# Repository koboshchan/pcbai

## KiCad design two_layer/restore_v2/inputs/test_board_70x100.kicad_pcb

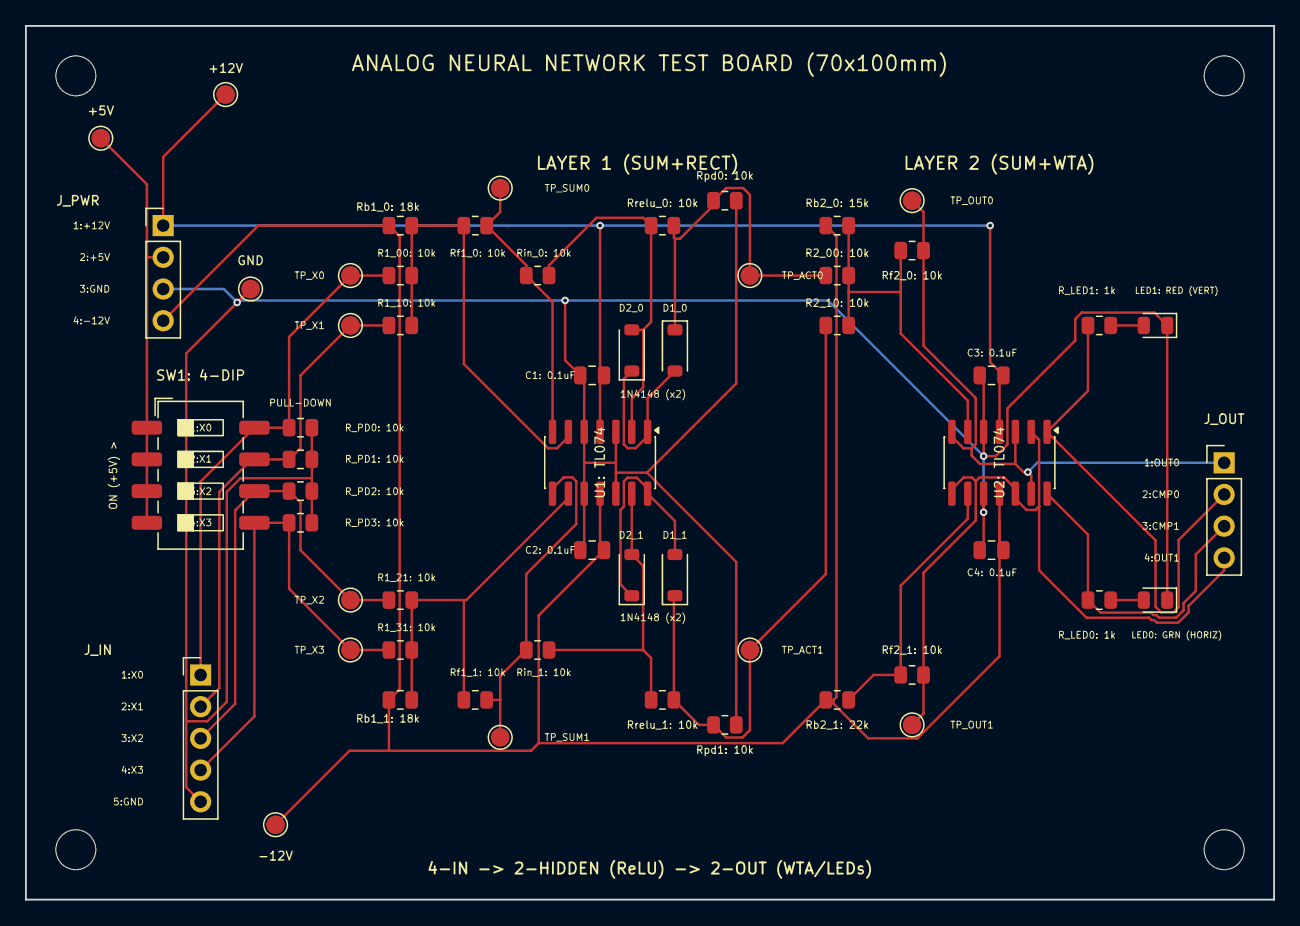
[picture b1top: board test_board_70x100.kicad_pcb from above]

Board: 2 copper layers, 100.0 x 70.0 mm, 60 parts (0 on the bottom side), 26 nets.

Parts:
C1, C2, C3, C4: 0.1uF; C_0805_2012Metric
D1_0, D1_1, D2_0, D2_1: 1N4148; D_SOD-123
H1, H2, H3, H4: M3; MountingHole_3.2mm_M3
J_IN: X0..X3/GND; PinHeader_1x05_P2.54mm_Vertical
J_OUT: OUT; PinHeader_1x04_P2.54mm_Vertical
J_PWR: PWR; PinHeader_1x04_P2.54mm_Vertical
LED0: Green_Horiz; LED_0805_2012Metric
LED1: Red_Vert; LED_0805_2012Metric
R1_00, R1_10, R1_21, R1_31, R2_00, R2_10: 10k; R_0805_2012Metric
R_LED0, R_LED1: 1k; R_0805_2012Metric
R_PD0, R_PD1, R_PD2, R_PD3: 10k; R_0805_2012Metric
Rb1_0, Rb1_1: 18k; R_0805_2012Metric
Rb2_0: 15k; R_0805_2012Metric
Rb2_1: 22k; R_0805_2012Metric
Rf1_0, Rf1_1, Rf2_0, Rf2_1: 10k; R_0805_2012Metric
Rin_0, Rin_1: 10k; R_0805_2012Metric
Rpd_act0, Rpd_act1: 10k; R_0805_2012Metric
Rrelu_0, Rrelu_1: 10k; R_0805_2012Metric
SW1: 4-DIP; SW_DIP_SPSTx04_Slide_6.7x11.72mm_W8.61mm_P2.54mm_LowProfile
TP_+5V: +5V; TestPoint_Pad_D1.5mm
TP_+12V: +12V; TestPoint_Pad_D1.5mm
TP_-12V: -12V; TestPoint_Pad_D1.5mm
TP_ACT0: V_ACT0; TestPoint_Pad_D1.5mm
TP_ACT1: V_ACT1; TestPoint_Pad_D1.5mm
TP_GND: GND; TestPoint_Pad_D1.5mm
TP_OUT0: V_OUT0; TestPoint_Pad_D1.5mm
TP_OUT1: V_OUT1; TestPoint_Pad_D1.5mm
TP_SUM0: V_SUM0; TestPoint_Pad_D1.5mm
TP_SUM1: V_SUM1; TestPoint_Pad_D1.5mm
TP_X0: X0; TestPoint_Pad_D1.5mm
TP_X1: X1; TestPoint_Pad_D1.5mm
TP_X2: X2; TestPoint_Pad_D1.5mm
TP_X3: X3; TestPoint_Pad_D1.5mm
U1, U2: TL074; SOIC-14_3.9x8.7mm_P1.27mm

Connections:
+5V: J_PWR.2, SW1.1, SW1.2, SW1.3, SW1.4, TP_+5V.1
+12V: C1.2, C3.2, J_PWR.1, TP_+12V.1, U1.4, U2.4
-12V: C2.2, C4.2, J_PWR.4, Rb1_0.1, Rb1_1.1, Rb2_0.1, Rb2_1.1, TP_-12V.1, U1.11, U2.11
CMP_OUT0: J_OUT.2, R_LED1.1, U2.1
CMP_OUT1: J_OUT.3, R_LED0.1, U2.14
GND: C1.1, C2.1, C3.1, C4.1, J_IN.5, J_PWR.3, LED0.1, LED1.1, R_PD0.2, R_PD1.2, R_PD2.2, R_PD3.2, Rpd_act0.2, Rpd_act1.2, TP_GND.1, U1.3, U1.5, U1.10, U1.12, U2.5, U2.10
LED0_A: LED0.2, R_LED0.2
LED1_A: LED1.2, R_LED1.2
RECT_NODE_0: D2_0.2, Rin_0.2, Rrelu_0.1, U1.2
RECT_NODE_1: D2_1.2, Rin_1.2, Rrelu_1.1, U1.13
RECT_OUT_0: D1_0.2, D2_0.1, U1.1
RECT_OUT_1: D1_1.2, D2_1.1, U1.14
SUM2_NODE_0: R2_00.2, R2_10.2, Rb2_0.2, Rf2_0.1, U2.6
SUM2_NODE_1: Rb2_1.2, Rf2_1.1, U2.9
SUM_NODE_0: R1_00.2, R1_10.2, Rb1_0.2, Rf1_0.1, U1.6
SUM_NODE_1: R1_21.2, R1_31.2, Rb1_1.2, Rf1_1.1, U1.9
V_ACT0: D1_0.1, R2_00.1, Rpd_act0.1, Rrelu_0.2, TP_ACT0.1
V_ACT1: D1_1.1, R2_10.1, Rpd_act1.1, Rrelu_1.2, TP_ACT1.1
V_OUT0: J_OUT.1, Rf2_0.2, TP_OUT0.1, U2.3, U2.7, U2.13
V_OUT1: J_OUT.4, Rf2_1.2, TP_OUT1.1, U2.2, U2.8, U2.12
V_SUM0: Rf1_0.2, Rin_0.1, TP_SUM0.1, U1.7
V_SUM1: Rf1_1.2, Rin_1.1, TP_SUM1.1, U1.8
X0: J_IN.1, R1_00.1, R_PD0.1, SW1.8, TP_X0.1
X1: J_IN.2, R1_10.1, R_PD1.1, SW1.7, TP_X1.1
X2: J_IN.3, R1_21.1, R_PD2.1, SW1.6, TP_X2.1
X3: J_IN.4, R1_31.1, R_PD3.1, SW1.5, TP_X3.1

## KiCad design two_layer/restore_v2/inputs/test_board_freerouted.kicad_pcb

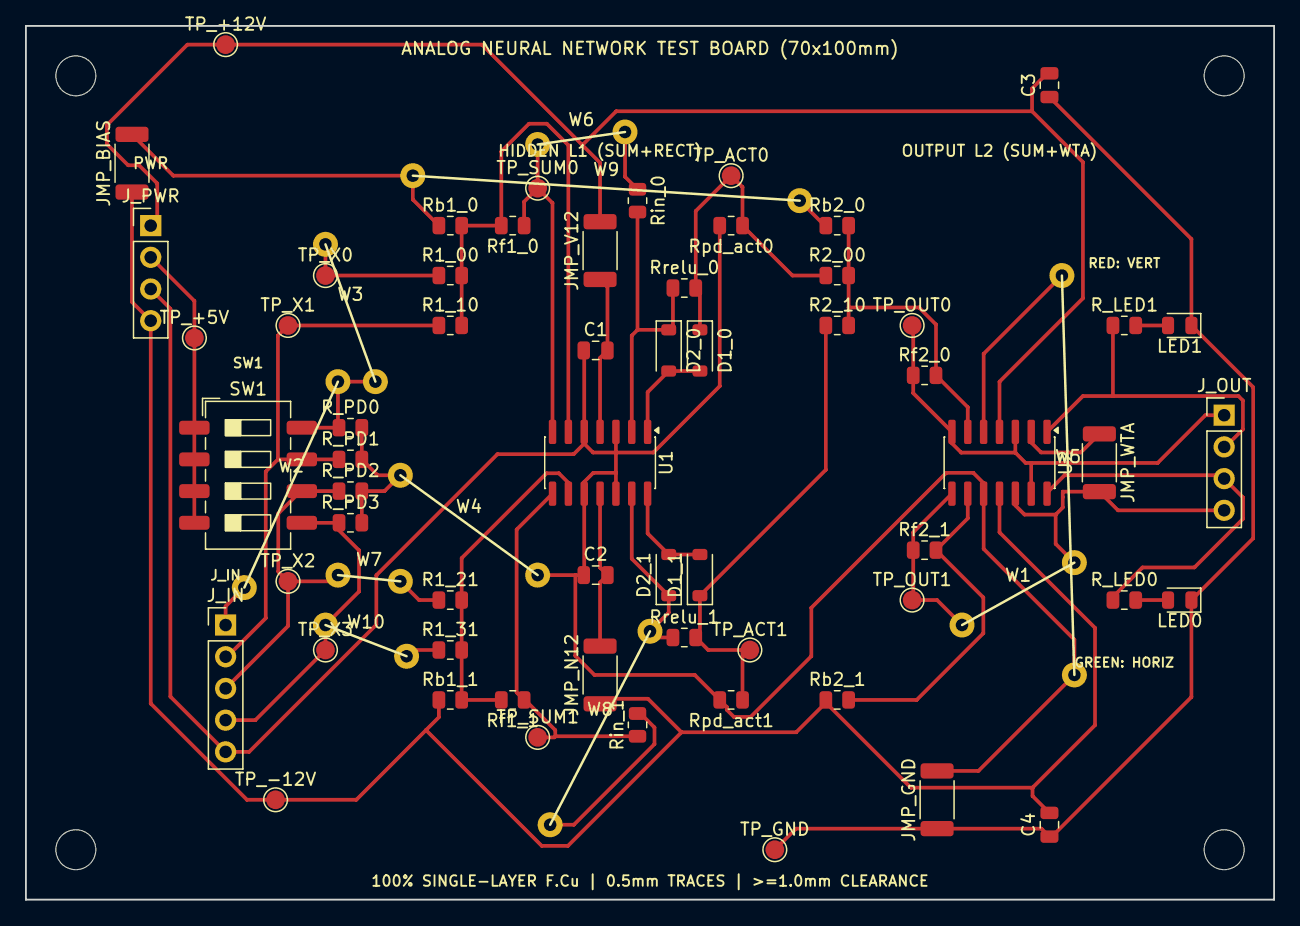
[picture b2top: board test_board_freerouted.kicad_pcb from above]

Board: 2 copper layers, 100.0 x 70.0 mm, 75 parts (0 on the bottom side), 41 nets.

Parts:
C1, C2, C3, C4: 0.1uF; C_0805_2012Metric
D1_0, D1_1, D2_0, D2_1: 1N4148; D_SOD-123
H1, H2, H3, H4: M3; MountingHole_3.2mm_M3
JMP_BIAS: 0R; R_2010_5025Metric
JMP_GND: 0R; R_2010_5025Metric
JMP_N12: 0R; R_2010_5025Metric
JMP_V12: 0R; R_2010_5025Metric
JMP_WTA: 0R; R_2010_5025Metric
J_IN: X0..X3/GND; PinHeader_1x05_P2.54mm_Vertical
J_OUT: OUT; PinHeader_1x04_P2.54mm_Vertical
J_PWR: PWR; PinHeader_1x04_P2.54mm_Vertical
LED0: Green_Horiz; LED_0805_2012Metric
LED1: Red_Vert; LED_0805_2012Metric
R1_00, R1_10, R1_21, R1_31, R2_00, R2_10: 10k; R_0805_2012Metric
R_LED0, R_LED1: 1k; R_0805_2012Metric
R_PD0, R_PD1, R_PD2, R_PD3: 10k; R_0805_2012Metric
Rb1_0, Rb1_1: 18k; R_0805_2012Metric
Rb2_0: 15k; R_0805_2012Metric
Rb2_1: 22k; R_0805_2012Metric
Rf1_0, Rf1_1, Rf2_0, Rf2_1: 10k; R_0805_2012Metric
Rin_0, Rin_1: 10k; R_0805_2012Metric
Rpd_act0, Rpd_act1: 10k; R_0805_2012Metric
Rrelu_0, Rrelu_1: 10k; R_0805_2012Metric
SW1: 4-DIP; SW_DIP_SPSTx04_Slide_6.7x11.72mm_W8.61mm_P2.54mm_LowProfile
TP_+5V: +5V; TestPoint_Pad_D1.5mm
TP_+12V: +12V; TestPoint_Pad_D1.5mm
TP_-12V: -12V; TestPoint_Pad_D1.5mm
TP_ACT0: V_ACT0; TestPoint_Pad_D1.5mm
TP_ACT1: V_ACT1; TestPoint_Pad_D1.5mm
TP_GND: GND_SOUTH; TestPoint_Pad_D1.5mm
TP_OUT0: V_OUT0; TestPoint_Pad_D1.5mm
TP_OUT1: V_OUT1; TestPoint_Pad_D1.5mm
TP_SUM0: V_SUM0; TestPoint_Pad_D1.5mm
TP_SUM1: V_SUM1; TestPoint_Pad_D1.5mm
TP_X0: X0; TestPoint_Pad_D1.5mm
TP_X1: X1; TestPoint_Pad_D1.5mm
TP_X2: X2; TestPoint_Pad_D1.5mm
TP_X3: X3; TestPoint_Pad_D1.5mm
U1, U2: TL074; SOIC-14_3.9x8.7mm_P1.27mm
W1, W2, W3, W4, W5, W6, W7, W8, W9, W10: Jumper_Wire

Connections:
+5V: J_PWR.2, SW1.1, SW1.2, SW1.3, SW1.4, TP_+5V.1
+12V: C3.2, JMP_V12.2, J_PWR.1, TP_+12V.1, U2.4
+12V_U1: C1.2, JMP_V12.1, U1.4
-12V: C4.2, JMP_BIAS.1, JMP_N12.1, J_PWR.4, Rb1_1.1, Rb2_1.1, TP_-12V.1, U2.11
-12V_NORTH: JMP_BIAS.2, Rb1_0.1, W9.2
-12V_NORTH_B: Rb2_0.1, W9.1
-12V_U1: C2.2, JMP_N12.2, U1.11
CMP_OUT0: J_OUT.2, R_LED1.1, U2.1
CMP_OUT1: J_OUT.3, R_LED0.1, U2.14
GND: C1.1, C2.1, JMP_GND.2, J_IN.5, J_PWR.3, Rpd_act0.2, Rpd_act1.2, U1.3, U1.5, U1.10, U1.12, U2.10, W4.2, W5.2
GND_SOUTH: C3.1, C4.1, JMP_GND.1, LED0.1, LED1.1, TP_GND.1
GND_U2_5: U2.5, W5.1
GND_WEST: R_PD0.2, R_PD1.2, R_PD2.2, R_PD3.2, W4.1
LED0_A: LED0.2, R_LED0.2
LED1_A: LED1.2, R_LED1.2
RECT_NODE_0: D2_0.1, Rin_0.2, Rrelu_0.1, U1.2
RECT_NODE_1: D2_1.1, Rrelu_1.1, U1.13, W8.2
RECT_NODE_1_IN: Rin_1.2, W8.1
RECT_OUT_0: D1_0.2, D2_0.2, U1.1
RECT_OUT_1: D1_1.2, D2_1.2, U1.14
SUM2_NODE_0: R2_00.2, R2_10.2, Rb2_0.2, Rf2_0.2, U2.6
SUM2_NODE_1: Rb2_1.2, Rf2_1.2, U2.9
SUM_NODE_0: R1_00.2, R1_10.2, Rb1_0.2, Rf1_0.2, U1.6
SUM_NODE_1: R1_21.2, R1_31.2, Rb1_1.2, Rf1_1.2, U1.9
V_ACT0: D1_0.1, R2_00.1, Rpd_act0.1, Rrelu_0.2, TP_ACT0.1
V_ACT1: D1_1.1, R2_10.1, Rpd_act1.1, Rrelu_1.2, TP_ACT1.1
V_OUT0: J_OUT.1, Rf2_0.1, TP_OUT0.1, U2.3, U2.7, U2.13
V_OUT1: JMP_WTA.2, J_OUT.4, U2.12, W1.2
V_OUT1_A: Rf2_1.1, TP_OUT1.1, U2.8, W1.1
V_OUT1_JMP: JMP_WTA.1, U2.2
V_SUM0: Rf1_0.1, TP_SUM0.1, U1.7, W6.2
V_SUM0_IN: Rin_0.1, W6.1
V_SUM1: Rf1_1.1, Rin_1.1, TP_SUM1.1, U1.8
X0: R_PD0.1, SW1.8, W2.2, W3.1
X0_IN: J_IN.1, W2.1
X0_NORTH: R1_00.1, TP_X0.1, W3.2
X1: J_IN.2, R1_10.1, R_PD1.1, SW1.7, TP_X1.1
X2: J_IN.3, R_PD2.1, SW1.6, TP_X2.1, W7.2
X2_R1: R1_21.1, W7.1
X3: J_IN.4, R_PD3.1, SW1.5, TP_X3.1, W10.1
X3_R1: R1_31.1, W10.2

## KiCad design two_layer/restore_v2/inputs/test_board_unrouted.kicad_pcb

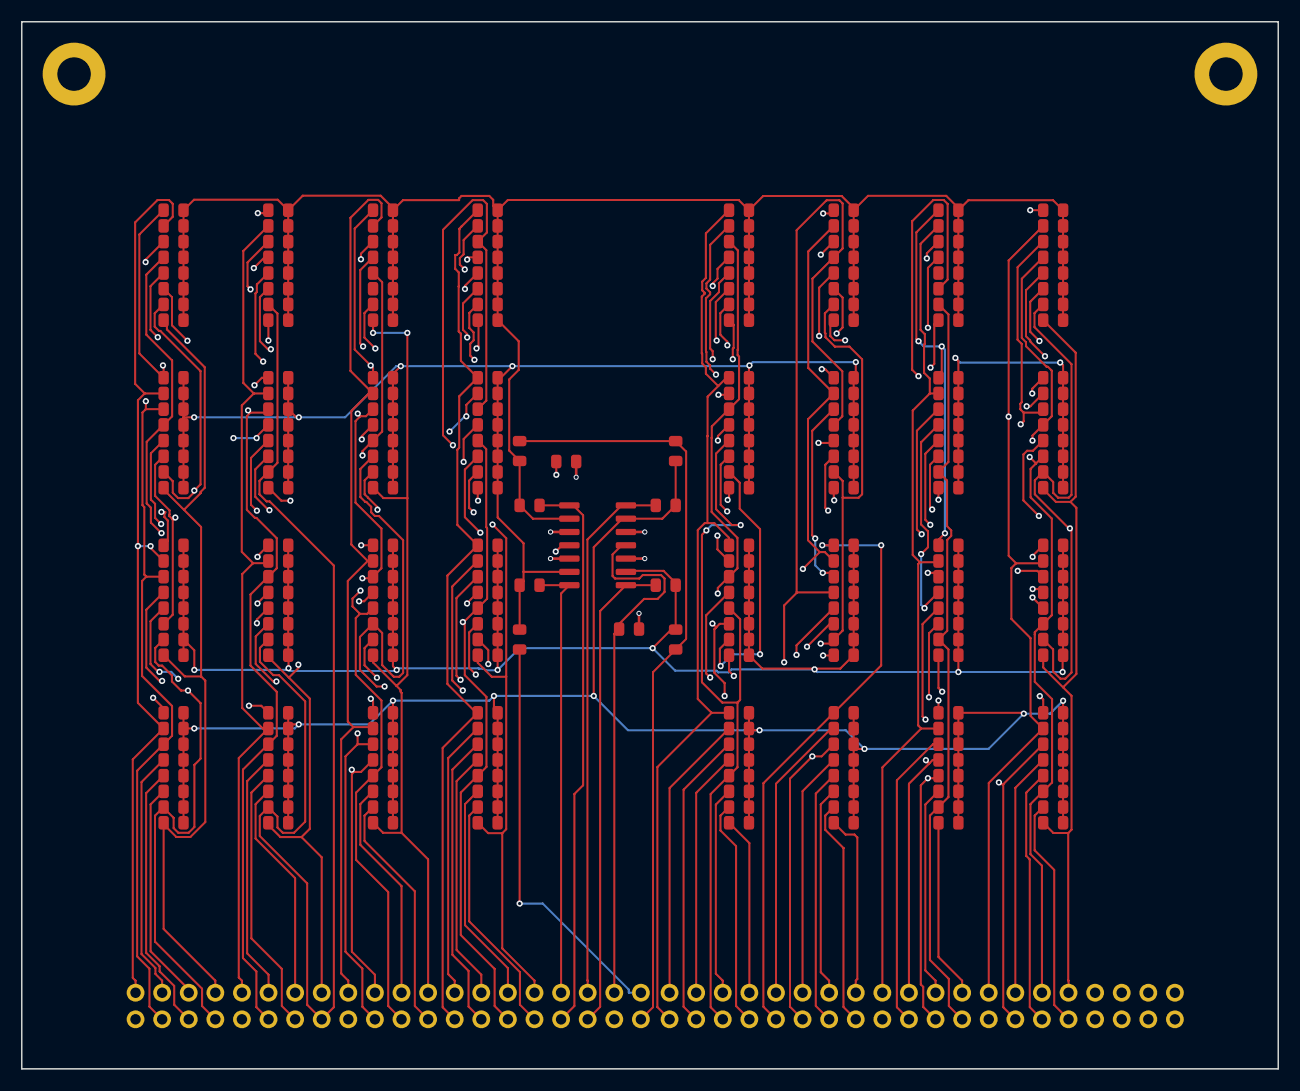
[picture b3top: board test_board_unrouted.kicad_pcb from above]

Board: 4 copper layers, 120.0 x 100.0 mm, 271 parts (0 on the bottom side), 77 nets.

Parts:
C_U1N, C_U1P: 0.1uF; C_0805_2012Metric
H1, H2: MountingHole_3.2mm_M3_Pad
J_SLOT_A: Inputs_0_31_and_Sums; PinHeader_2x20_P2.54mm_Vertical
J_SLOT_B: Inputs_32_63_and_GND; PinHeader_2x20_P2.54mm_Vertical
R1_0_0, R1_0_1, R1_0_2, R1_0_3, R1_1_3, R1_2_3, R1_3_3, R1_4_3, R1_5_3, R1_7_3, R1_8_1, R1_8_3, R1_9_3, R1_10_3, R1_12_3, R1_13_3, R1_15_3, R1_16_1, R1_16_3, R1_17_3, R1_18_3, R1_19_3, R1_20_3, R1_21_3, R1_22_3, R1_23_3, R1_24_3, R1_25_3, R1_26_3, R1_27_3, R1_28_3, R1_29_3, R1_30_3, R1_31_0, R1_31_1, R1_31_2, R1_31_3, R1_32_0, R1_32_1, R1_32_2, R1_32_3, R1_33_3, R1_34_3, R1_35_3, R1_36_3, R1_37_3, R1_38_3, R1_39_0, R1_39_1, R1_39_2, R1_39_3, R1_40_0, R1_40_1, R1_40_2, R1_40_3, R1_41_3, R1_42_3, R1_43_3, R1_44_3, R1_45_3, R1_46_3, R1_47_3, R1_48_3, R1_49_3, R1_50_3, R1_51_3, R1_52_3, R1_53_3, R1_54_3, R1_55_3, R1_56_3, R1_57_3, R1_58_3, R1_59_3, R1_60_3, R1_61_3, R1_62_3, R1_63_3: DNP; R_0805_2012Metric
R1_1_0, R1_33_2, R1_51_0: 34k; R_0805_2012Metric
R1_1_1, R1_50_0: 105k; R_0805_2012Metric
R1_1_2: 24.3k; R_0805_2012Metric
R1_2_0, R1_2_1, R1_5_0: 20.5k; R_0805_2012Metric
R1_2_2, R1_61_1: 30.9k; R_0805_2012Metric
R1_3_0, R1_11_1, R1_27_2, R1_62_0: 54.9k; R_0805_2012Metric
R1_3_1, R1_17_1, R1_38_2: 19.6k; R_0805_2012Metric
R1_3_2: 137k; R_0805_2012Metric
R1_4_0, R1_42_2: 37.4k; R_0805_2012Metric
R1_4_1, R1_29_1, R1_44_2: 21.5k; R_0805_2012Metric
R1_4_2, R1_41_2, R1_62_2: 20k; R_0805_2012Metric
R1_5_1, R1_58_0: 51.1k; R_0805_2012Metric
R1_5_2, R1_12_0: 41.2k; R_0805_2012Metric
R1_6_0: 10k; R_0805_2012Metric
R1_6_1, R1_38_0: 16.9k; R_0805_2012Metric
R1_6_2, R1_50_2: 60.4k; R_0805_2012Metric
R1_6_3, R1_8_0, R1_8_2, R1_11_3, R1_14_3, R1_23_1, R1_23_2, R1_48_1, R1_56_1: 9.76M; R_0805_2012Metric
R1_7_0: 24.9k; R_0805_2012Metric
R1_7_1: 2.15M; R_0805_2012Metric
R1_7_2, R1_13_0, R1_21_2: 22.6k; R_0805_2012Metric
R1_9_0, R1_13_2, R1_42_1, R1_50_1: 15.4k; R_0805_2012Metric
R1_9_1: 15k; R_0805_2012Metric
R1_9_2, R1_14_1, R1_57_2: 17.8k; R_0805_2012Metric
R1_10_0, R1_11_2, R1_27_0: 64.9k; R_0805_2012Metric
R1_10_1, R1_25_1, R1_35_1, R1_44_0, R1_52_1, R1_63_0: 14.7k; R_0805_2012Metric
R1_10_2, R1_15_2, R1_34_1: 40.2k; R_0805_2012Metric
R1_11_0, R1_63_2: 71.5k; R_0805_2012Metric
R1_12_1: 143k; R_0805_2012Metric
R1_12_2: 255k; R_0805_2012Metric
R1_13_1, R1_14_2: 23.2k; R_0805_2012Metric
R1_14_0, R1_29_2: 90.9k; R_0805_2012Metric
R1_15_0: 178k; R_0805_2012Metric
R1_15_1: 3.01M; R_0805_2012Metric
R1_16_0, R1_43_2: 68.1k; R_0805_2012Metric
R1_16_2: 150k; R_0805_2012Metric
R1_17_0, R1_29_0, R1_63_1: 69.8k; R_0805_2012Metric
R1_17_2, R1_20_1, R1_37_0: 29.4k; R_0805_2012Metric
R1_18_0: 82.5k; R_0805_2012Metric
R1_18_1: 56.2k; R_0805_2012Metric
R1_18_2, R1_49_1, R1_59_0: 52.3k; R_0805_2012Metric
R1_19_0, R1_58_2: 28k; R_0805_2012Metric
R1_19_1: 15.8k; R_0805_2012Metric
R1_19_2: 17.4k; R_0805_2012Metric
R1_20_0, R1_22_2, R1_46_1: 12.1k; R_0805_2012Metric
R1_20_2: 1.07M; R_0805_2012Metric
R1_21_0: 8.45k; R_0805_2012Metric
R1_21_1: 9.76k; R_0805_2012Metric
R1_22_0: 11k; R_0805_2012Metric
R1_22_1, R1_52_0: 97.6k; R_0805_2012Metric
R1_23_0: 130k; R_0805_2012Metric
R1_24_0: 162k; R_0805_2012Metric
R1_24_1: 953k; R_0805_2012Metric
R1_24_2: 511k; R_0805_2012Metric
R1_25_0, R1_36_2: 45.3k; R_0805_2012Metric
R1_25_2, R1_28_0, R1_36_0: 14.3k; R_0805_2012Metric
R1_26_0, R1_26_1, R1_53_1: 26.7k; R_0805_2012Metric
R1_26_2, R1_60_2: 42.2k; R_0805_2012Metric
R1_27_1, R1_41_0, R1_59_1: 23.7k; R_0805_2012Metric
R1_28_1: 14k; R_0805_2012Metric
R1_28_2: 110k; R_0805_2012Metric
R1_30_0: 100k; R_0805_2012Metric
R1_30_1: 27.4k; R_0805_2012Metric
R1_30_2: 13.7k; R_0805_2012Metric
R1_33_0: 9.09k; R_0805_2012Metric
R1_33_1: 9.31k; R_0805_2012Metric
R1_34_0: 43.2k; R_0805_2012Metric
R1_34_2: 84.5k; R_0805_2012Metric
R1_35_0: 182k; R_0805_2012Metric
R1_35_2, R1_37_2: 46.4k; R_0805_2012Metric
R1_36_1, R1_51_2: 49.9k; R_0805_2012Metric
R1_37_1: 11.8k; R_0805_2012Metric
R1_38_1: 8.87k; R_0805_2012Metric
R1_41_1: 12.4k; R_0805_2012Metric
R1_42_0, R1_54_2: 66.5k; R_0805_2012Metric
R1_43_0, R1_45_2: 13.3k; R_0805_2012Metric
R1_43_1, R1_49_0: 34.8k; R_0805_2012Metric
R1_44_1: 16.2k; R_0805_2012Metric
R1_45_0: 48.7k; R_0805_2012Metric
R1_45_1: 9.53k; R_0805_2012Metric
R1_46_0: 30.1k; R_0805_2012Metric
R1_46_2: 18.7k; R_0805_2012Metric
R1_47_0: 787k; R_0805_2012Metric
R1_47_1: 210k; R_0805_2012Metric
R1_47_2: 3.09M; R_0805_2012Metric
R1_48_0: 750k; R_0805_2012Metric
R1_48_2, R1_57_1: 845k; R_0805_2012Metric
R1_49_2, R1_57_0, R1_58_1: 57.6k; R_0805_2012Metric
R1_51_1: 44.2k; R_0805_2012Metric
R1_52_2, R1_53_2: 18.2k; R_0805_2012Metric
R1_53_0: 19.1k; R_0805_2012Metric
R1_54_0: 11.3k; R_0805_2012Metric
R1_54_1: 294k; R_0805_2012Metric
R1_55_0: 10.7k; R_0805_2012Metric
R1_55_1: 121k; R_0805_2012Metric
R1_55_2: 75k; R_0805_2012Metric
R1_56_0: 2.05M; R_0805_2012Metric
R1_56_2: 2.74M; R_0805_2012Metric
R1_59_2: 681k; R_0805_2012Metric
R1_60_0: 158k; R_0805_2012Metric
R1_60_1, R1_62_1: 22.1k; R_0805_2012Metric
R1_61_0: 165k; R_0805_2012Metric
R1_61_2: 16.5k; R_0805_2012Metric
Rb_N0: 324k; R_0805_2012Metric
Rb_N1: 332k; R_0805_2012Metric
Rb_N2: 140k; R_0805_2012Metric
Rb_N3: 549k; R_0805_2012Metric
Rf_N0, Rf_N1, Rf_N2, Rf_N3: 10k; R_0805_2012Metric
U1: TL074; SOIC-14_3.9x8.7mm_P1.27mm

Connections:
+5V_REF: J_SLOT_A.39, Rb_N0.2, Rb_N2.1, Rb_N3.2
+12V: C_U1P.1, J_SLOT_A.37, U1.4
-5V_REF: J_SLOT_A.40, Rb_N1.1
-12V: C_U1N.1, J_SLOT_A.38, U1.11
GND: C_U1N.2, C_U1P.2, H1.1, H2.1, J_SLOT_B.33, J_SLOT_B.34, J_SLOT_B.35, J_SLOT_B.36, J_SLOT_B.37, J_SLOT_B.38, J_SLOT_B.39, J_SLOT_B.40, U1.3, U1.5, U1.10, U1.12
INV_N0: R1_0_0.2, R1_1_0.2, R1_2_0.2, R1_3_0.2, R1_4_0.2, R1_5_0.2, R1_6_0.2, R1_7_0.2, R1_8_0.2, R1_9_0.2, R1_10_0.2, R1_11_0.2, R1_12_0.2, R1_13_0.2, R1_14_0.2, R1_15_0.2, R1_16_0.2, R1_17_0.2, R1_18_0.2, R1_19_0.2, R1_20_0.2, R1_21_0.2, R1_22_0.2, R1_23_0.2, R1_24_0.2, R1_25_0.2, R1_26_0.2, R1_27_0.2, R1_28_0.2, R1_29_0.2, R1_30_0.2, R1_31_0.2, R1_32_0.2, R1_33_0.2, R1_34_0.2, R1_35_0.2, R1_36_0.2, R1_37_0.2, R1_38_0.2, R1_39_0.2, R1_40_0.2, R1_41_0.2, R1_42_0.2, R1_43_0.2, R1_44_0.2, R1_45_0.2, R1_46_0.2, R1_47_0.2, R1_48_0.2, R1_49_0.2, R1_50_0.2, R1_51_0.2, R1_52_0.2, R1_53_0.2, R1_54_0.2, R1_55_0.2, R1_56_0.2, R1_57_0.2, R1_58_0.2, R1_59_0.2, R1_60_0.2, R1_61_0.2, R1_62_0.2, R1_63_0.2, Rb_N0.1, Rf_N0.1, U1.2
INV_N1: R1_0_1.2, R1_1_1.2, R1_2_1.2, R1_3_1.2, R1_4_1.2, R1_5_1.2, R1_6_1.2, R1_7_1.2, R1_8_1.2, R1_9_1.2, R1_10_1.2, R1_11_1.2, R1_12_1.2, R1_13_1.2, R1_14_1.2, R1_15_1.2, R1_16_1.2, R1_17_1.2, R1_18_1.2, R1_19_1.2, R1_20_1.2, R1_21_1.2, R1_22_1.2, R1_23_1.2, R1_24_1.2, R1_25_1.2, R1_26_1.2, R1_27_1.2, R1_28_1.2, R1_29_1.2, R1_30_1.2, R1_31_1.2, R1_32_1.2, R1_33_1.2, R1_34_1.2, R1_35_1.2, R1_36_1.2, R1_37_1.2, R1_38_1.2, R1_39_1.2, R1_40_1.2, R1_41_1.2, R1_42_1.2, R1_43_1.2, R1_44_1.2, R1_45_1.2, R1_46_1.2, R1_47_1.2, R1_48_1.2, R1_49_1.2, R1_50_1.2, R1_51_1.2, R1_52_1.2, R1_53_1.2, R1_54_1.2, R1_55_1.2, R1_56_1.2, R1_57_1.2, R1_58_1.2, R1_59_1.2, R1_60_1.2, R1_61_1.2, R1_62_1.2, R1_63_1.2, Rb_N1.2, Rf_N1.1, U1.6
INV_N2: R1_0_2.2, R1_1_2.2, R1_2_2.2, R1_3_2.2, R1_4_2.2, R1_5_2.2, R1_6_2.2, R1_7_2.2, R1_8_2.2, R1_9_2.2, R1_10_2.2, R1_11_2.2, R1_12_2.2, R1_13_2.2, R1_14_2.2, R1_15_2.2, R1_16_2.2, R1_17_2.2, R1_18_2.2, R1_19_2.2, R1_20_2.2, R1_21_2.2, R1_22_2.2, R1_23_2.2, R1_24_2.2, R1_25_2.2, R1_26_2.2, R1_27_2.2, R1_28_2.2, R1_29_2.2, R1_30_2.2, R1_31_2.2, R1_32_2.2, R1_33_2.2, R1_34_2.2, R1_35_2.2, R1_36_2.2, R1_37_2.2, R1_38_2.2, R1_39_2.2, R1_40_2.2, R1_41_2.2, R1_42_2.2, R1_43_2.2, R1_44_2.2, R1_45_2.2, R1_46_2.2, R1_47_2.2, R1_48_2.2, R1_49_2.2, R1_50_2.2, R1_51_2.2, R1_52_2.2, R1_53_2.2, R1_54_2.2, R1_55_2.2, R1_56_2.2, R1_57_2.2, R1_58_2.2, R1_59_2.2, R1_60_2.2, R1_61_2.2, R1_62_2.2, R1_63_2.2, Rb_N2.2, Rf_N2.2, U1.9
INV_N3: R1_0_3.2, R1_1_3.2, R1_2_3.2, R1_3_3.2, R1_4_3.2, R1_5_3.2, R1_6_3.2, R1_7_3.2, R1_8_3.2, R1_9_3.2, R1_10_3.2, R1_11_3.2, R1_12_3.2, R1_13_3.2, R1_14_3.2, R1_15_3.2, R1_16_3.2, R1_17_3.2, R1_18_3.2, R1_19_3.2, R1_20_3.2, R1_21_3.2, R1_22_3.2, R1_23_3.2, R1_24_3.2, R1_25_3.2, R1_26_3.2, R1_27_3.2, R1_28_3.2, R1_29_3.2, R1_30_3.2, R1_31_3.2, R1_32_3.2, R1_33_3.2, R1_34_3.2, R1_35_3.2, R1_36_3.2, R1_37_3.2, R1_38_3.2, R1_39_3.2, R1_40_3.2, R1_41_3.2, R1_42_3.2, R1_43_3.2, R1_44_3.2, R1_45_3.2, R1_46_3.2, R1_47_3.2, R1_48_3.2, R1_49_3.2, R1_50_3.2, R1_51_3.2, R1_52_3.2, R1_53_3.2, R1_54_3.2, R1_55_3.2, R1_56_3.2, R1_57_3.2, R1_58_3.2, R1_59_3.2, R1_60_3.2, R1_61_3.2, R1_62_3.2, R1_63_3.2, Rb_N3.1, Rf_N3.2, U1.13
IN_0: J_SLOT_A.1, R1_0_0.1, R1_0_1.1, R1_0_2.1, R1_0_3.1
IN_1: J_SLOT_A.2, R1_1_0.1, R1_1_1.1, R1_1_2.1, R1_1_3.1
IN_2: J_SLOT_A.3, R1_2_0.1, R1_2_1.1, R1_2_2.1, R1_2_3.1
IN_3: J_SLOT_A.4, R1_3_0.1, R1_3_1.1, R1_3_2.1, R1_3_3.1
IN_4: J_SLOT_A.5, R1_4_0.1, R1_4_1.1, R1_4_2.1, R1_4_3.1
IN_5: J_SLOT_A.6, R1_5_0.1, R1_5_1.1, R1_5_2.1, R1_5_3.1
IN_6: J_SLOT_A.7, R1_6_0.1, R1_6_1.1, R1_6_2.1, R1_6_3.1
IN_7: J_SLOT_A.8, R1_7_0.1, R1_7_1.1, R1_7_2.1, R1_7_3.1
IN_8: J_SLOT_A.9, R1_8_0.1, R1_8_1.1, R1_8_2.1, R1_8_3.1
IN_9: J_SLOT_A.10, R1_9_0.1, R1_9_1.1, R1_9_2.1, R1_9_3.1
IN_10: J_SLOT_A.11, R1_10_0.1, R1_10_1.1, R1_10_2.1, R1_10_3.1
IN_11: J_SLOT_A.12, R1_11_0.1, R1_11_1.1, R1_11_2.1, R1_11_3.1
IN_12: J_SLOT_A.13, R1_12_0.1, R1_12_1.1, R1_12_2.1, R1_12_3.1
IN_13: J_SLOT_A.14, R1_13_0.1, R1_13_1.1, R1_13_2.1, R1_13_3.1
IN_14: J_SLOT_A.15, R1_14_0.1, R1_14_1.1, R1_14_2.1, R1_14_3.1
IN_15: J_SLOT_A.16, R1_15_0.1, R1_15_1.1, R1_15_2.1, R1_15_3.1
IN_16: J_SLOT_A.17, R1_16_0.1, R1_16_1.1, R1_16_2.1, R1_16_3.1
IN_17: J_SLOT_A.18, R1_17_0.1, R1_17_1.1, R1_17_2.1, R1_17_3.1
IN_18: J_SLOT_A.19, R1_18_0.1, R1_18_1.1, R1_18_2.1, R1_18_3.1
IN_19: J_SLOT_A.20, R1_19_0.1, R1_19_1.1, R1_19_2.1, R1_19_3.1
IN_20: J_SLOT_A.21, R1_20_0.1, R1_20_1.1, R1_20_2.1, R1_20_3.1
IN_21: J_SLOT_A.22, R1_21_0.1, R1_21_1.1, R1_21_2.1, R1_21_3.1
IN_22: J_SLOT_A.23, R1_22_0.1, R1_22_1.1, R1_22_2.1, R1_22_3.1
IN_23: J_SLOT_A.24, R1_23_0.1, R1_23_1.1, R1_23_2.1, R1_23_3.1
IN_24: J_SLOT_A.25, R1_24_0.1, R1_24_1.1, R1_24_2.1, R1_24_3.1
IN_25: J_SLOT_A.26, R1_25_0.1, R1_25_1.1, R1_25_2.1, R1_25_3.1
IN_26: J_SLOT_A.27, R1_26_0.1, R1_26_1.1, R1_26_2.1, R1_26_3.1
IN_27: J_SLOT_A.28, R1_27_0.1, R1_27_1.1, R1_27_2.1, R1_27_3.1
IN_28: J_SLOT_A.29, R1_28_0.1, R1_28_1.1, R1_28_2.1, R1_28_3.1
IN_29: J_SLOT_A.30, R1_29_0.1, R1_29_1.1, R1_29_2.1, R1_29_3.1
IN_30: J_SLOT_A.31, R1_30_0.1, R1_30_1.1, R1_30_2.1, R1_30_3.1
IN_31: J_SLOT_A.32, R1_31_0.1, R1_31_1.1, R1_31_2.1, R1_31_3.1
IN_32: J_SLOT_B.1, R1_32_0.1, R1_32_1.1, R1_32_2.1, R1_32_3.1
IN_33: J_SLOT_B.2, R1_33_0.1, R1_33_1.1, R1_33_2.1, R1_33_3.1
IN_34: J_SLOT_B.3, R1_34_0.1, R1_34_1.1, R1_34_2.1, R1_34_3.1
IN_35: J_SLOT_B.4, R1_35_0.1, R1_35_1.1, R1_35_2.1, R1_35_3.1
IN_36: J_SLOT_B.5, R1_36_0.1, R1_36_1.1, R1_36_2.1, R1_36_3.1
IN_37: J_SLOT_B.6, R1_37_0.1, R1_37_1.1, R1_37_2.1, R1_37_3.1
IN_38: J_SLOT_B.7, R1_38_0.1, R1_38_1.1, R1_38_2.1, R1_38_3.1
IN_39: J_SLOT_B.8, R1_39_0.1, R1_39_1.1, R1_39_2.1, R1_39_3.1
IN_40: J_SLOT_B.9, R1_40_0.1, R1_40_1.1, R1_40_2.1, R1_40_3.1
IN_41: J_SLOT_B.10, R1_41_0.1, R1_41_1.1, R1_41_2.1, R1_41_3.1
IN_42: J_SLOT_B.11, R1_42_0.1, R1_42_1.1, R1_42_2.1, R1_42_3.1
IN_43: J_SLOT_B.12, R1_43_0.1, R1_43_1.1, R1_43_2.1, R1_43_3.1
IN_44: J_SLOT_B.13, R1_44_0.1, R1_44_1.1, R1_44_2.1, R1_44_3.1
IN_45: J_SLOT_B.14, R1_45_0.1, R1_45_1.1, R1_45_2.1, R1_45_3.1
IN_46: J_SLOT_B.15, R1_46_0.1, R1_46_1.1, R1_46_2.1, R1_46_3.1
IN_47: J_SLOT_B.16, R1_47_0.1, R1_47_1.1, R1_47_2.1, R1_47_3.1
IN_48: J_SLOT_B.17, R1_48_0.1, R1_48_1.1, R1_48_2.1, R1_48_3.1
IN_49: J_SLOT_B.18, R1_49_0.1, R1_49_1.1, R1_49_2.1, R1_49_3.1
IN_50: J_SLOT_B.19, R1_50_0.1, R1_50_1.1, R1_50_2.1, R1_50_3.1
IN_51: J_SLOT_B.20, R1_51_0.1, R1_51_1.1, R1_51_2.1, R1_51_3.1
IN_52: J_SLOT_B.21, R1_52_0.1, R1_52_1.1, R1_52_2.1, R1_52_3.1
IN_53: J_SLOT_B.22, R1_53_0.1, R1_53_1.1, R1_53_2.1, R1_53_3.1
IN_54: J_SLOT_B.23, R1_54_0.1, R1_54_1.1, R1_54_2.1, R1_54_3.1
IN_55: J_SLOT_B.24, R1_55_0.1, R1_55_1.1, R1_55_2.1, R1_55_3.1
IN_56: J_SLOT_B.25, R1_56_0.1, R1_56_1.1, R1_56_2.1, R1_56_3.1
IN_57: J_SLOT_B.26, R1_57_0.1, R1_57_1.1, R1_57_2.1, R1_57_3.1
IN_58: J_SLOT_B.27, R1_58_0.1, R1_58_1.1, R1_58_2.1, R1_58_3.1
IN_59: J_SLOT_B.28, R1_59_0.1, R1_59_1.1, R1_59_2.1, R1_59_3.1
IN_60: J_SLOT_B.29, R1_60_0.1, R1_60_1.1, R1_60_2.1, R1_60_3.1
IN_61: J_SLOT_B.30, R1_61_0.1, R1_61_1.1, R1_61_2.1, R1_61_3.1
IN_62: J_SLOT_B.31, R1_62_0.1, R1_62_1.1, R1_62_2.1, R1_62_3.1
IN_63: J_SLOT_B.32, R1_63_0.1, R1_63_1.1, R1_63_2.1, R1_63_3.1
V_SUM_0: J_SLOT_A.33, Rf_N0.2, U1.1
V_SUM_1: J_SLOT_A.34, Rf_N1.2, U1.7
V_SUM_2: J_SLOT_A.35, Rf_N2.1, U1.8
V_SUM_3: J_SLOT_A.36, Rf_N3.1, U1.14
